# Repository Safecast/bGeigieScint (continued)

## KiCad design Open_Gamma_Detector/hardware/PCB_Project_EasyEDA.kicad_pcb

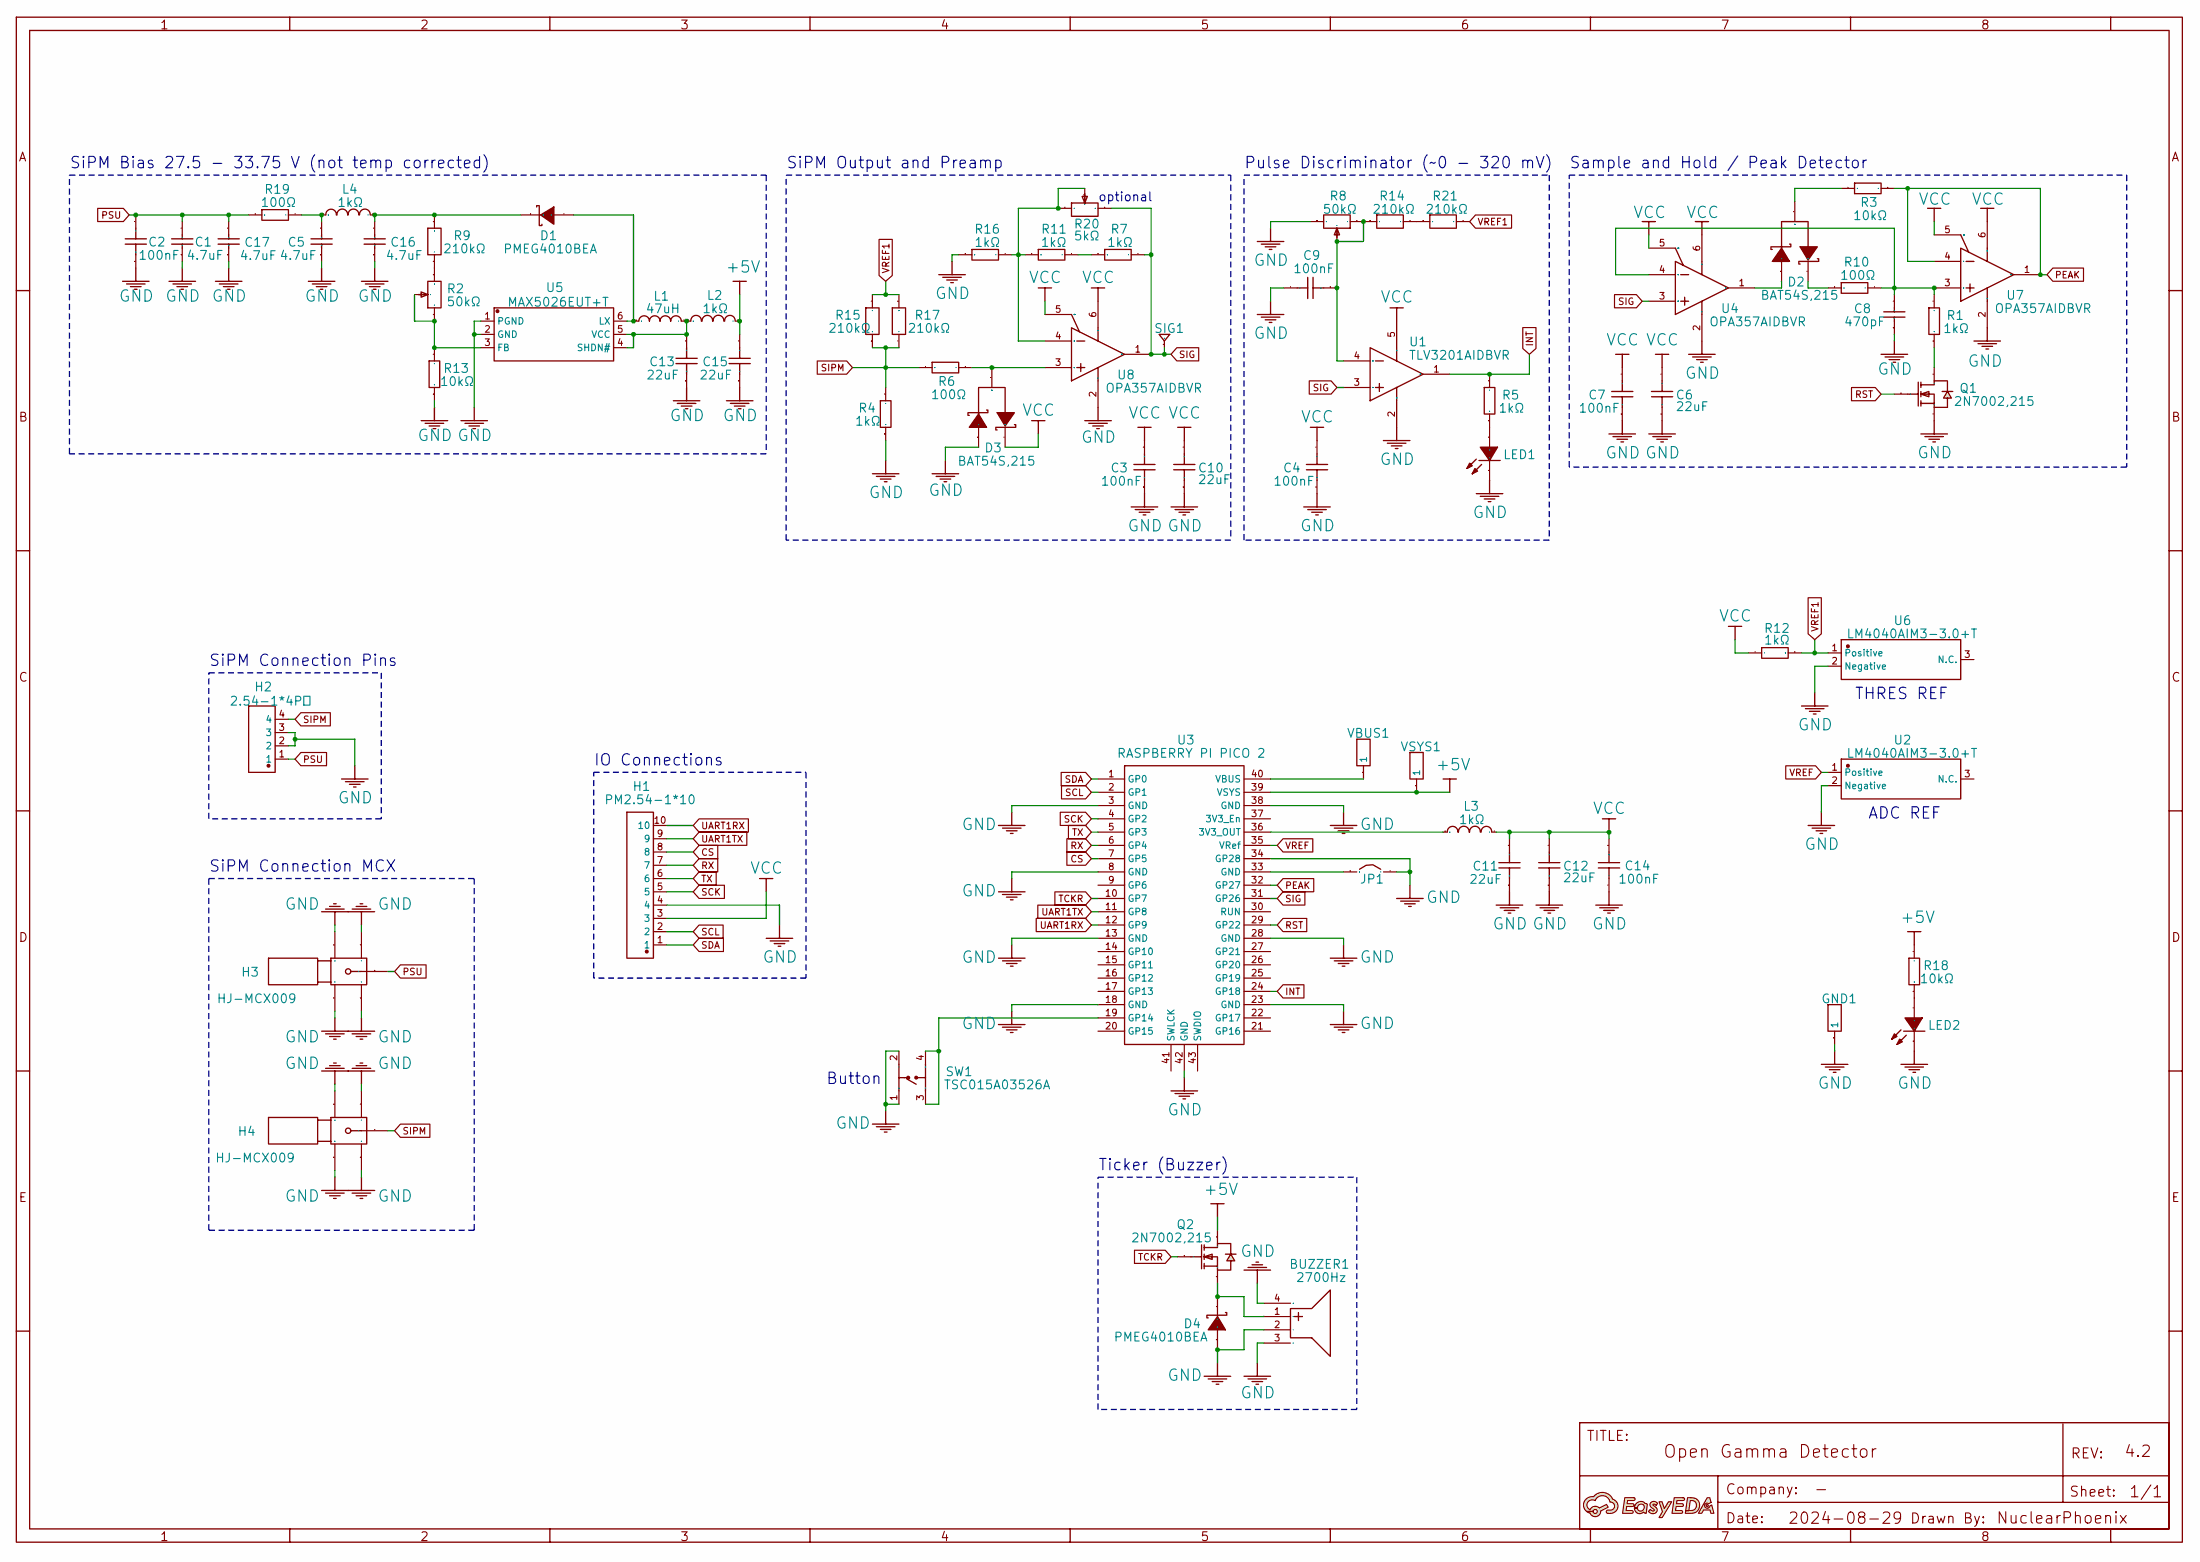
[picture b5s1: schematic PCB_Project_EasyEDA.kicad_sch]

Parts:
BUZZER1: 2700Hz; Manufacturer Part MLT-7525
C1, C5, C16, C17: 4.7uF; Manufacturer Part CL21A475KBQNNNE
C2, C3, C4, C7, C9, C14: 100nF; Manufacturer Part CL10B104KC8NNNC
C6, C10, C11, C12, C13, C15: 22uF; Manufacturer Part CL10A226MP8NUNE
C8: 470pF; Manufacturer Part ECHU1C471JX5
D1, D4: PMEG4010BEA; Manufacturer Part PMEG4010BEA,115
D2, D3: BAT54S,215; Manufacturer Part BAT54S,215
GND1: HDR-M-2.54_1x1
H1: PM2.54-1*10; Manufacturer Part PM2.54-1*10
H2: 2.54-1*4P母; Manufacturer Part 2.54-1*4P母
H3, H4: HJ-MCX009; Manufacturer Part HJ-MCX009
JP1: Jumper
L1: 47uH; Manufacturer Part NRS4018T470MDGJ
L2, L3, L4: 1kΩ; Manufacturer Part BLM18KG102SN1D
LED1, LED2: LTST-C190KGKT; Manufacturer Part LTST-C190KGKT
NO1: NO; Manufacturer Part ?
Q1, Q2: 2N7002,215; Manufacturer Part 2N7002,215
R1, R4, R5, R7, R11, R12, R16: 1kΩ; Manufacturer Part ARG03BTC1001
R2, R8: 50kΩ; Manufacturer Part 3296W-1-503LF
R3, R13, R18: 10kΩ; Manufacturer Part ARG03FTC1002
R6, R10, R19: 100Ω; Manufacturer Part 0603WAF1000T5E
R9, R14, R15, R17, R21: 210kΩ; Manufacturer Part TC0325D2103T5H
R20: 5kΩ; Manufacturer Part 3314J-1-502E
SIG1: TEST-POINT
SW1: TSC015A03526A; Manufacturer Part TSC015A03526A
U1: TLV3201AIDBVR; Manufacturer Part TLV3201AIDBVR
U2, U6: LM4040AIM3-3.0+T; Manufacturer Part LM4040AIM3-3.0+T
U3: RASPBERRY PI PICO 2; Manufacturer Part SC1631
U4, U7, U8: OPA357AIDBVR; Manufacturer Part OPA357AIDBVR
U5: MAX5026EUT+T; Manufacturer Part MAX5026EUT+T
VBUS1: HDR-M-2.54_1x1
VSYS1: HDR-M-2.54_1x1

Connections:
+5V: C15.2, L2.2, Q2.3 (D), R18.2, U3.39 (VSYS), VSYS1.1
CS: H1.8, U3.7 (GP5)
GND: BUZZER1.2 (-), BUZZER1.3, BUZZER1.4, C1.1, C2.1, C3.1, C4.1, C5.1, C6.1, C7.1, C8.1, C9.2, C10.1, C11.1, C12.1, C13.1, C14.2, C15.1, C16.1, C17.1, D3.1 (A), D4.2 (A), GND1.1, H1.4, H2.2, H2.3, H3.1, H3.2, H3.3, H3.4, H4.1, H4.2, H4.3, H4.4, JP1.2, LED1.1 (-), LED2.1 (-), Q1.2 (S), R4.1, R8.1, R13.1, R16.1, SW1.1, SW1.2, U1.2 (GND), U2.2 (Negative), U3.3 (GND), U3.8 (GND), U3.13 (GND), U3.18 (GND), U3.23 (GND), U3.28 (GND), U3.34 (GP28), U3.38 (GND), U3.42 (GND), U4.2 (V-), U5.1 (PGND), U5.2 (GND), U6.2 (Negative), U7.2 (V-), U8.2 (V-); also elsewhere on the board
INT: R5.2, U1.1 (OUT), U3.24 (GP18)
unnamed: BUZZER1.1 (+), D4.1 (K), Q2.2 (S)
unnamed: C5.2, L4.1, R19.2
unnamed: D1.2 (A), L1.1, U5.6 (LX)
unnamed: C16.2, D1.1 (K), L4.2, R9.1
unnamed: D2.1 (A), U4.1 (OUT)
unnamed: D2.3 (AK), R3.2
unnamed: D2.2 (K), R10.1
unnamed: D3.3 (AK), R6.2, U8.3 (IN+)
unnamed: JP1.1, U3.33 (GND)
unnamed: LED1.2 (+), R5.1
unnamed: LED2.2 (+), R18.1
unnamed: Q1.3 (D), R1.1
unnamed: R2.1, R9.2
unnamed: R7.1, R11.2
unnamed: R14.2, R21.1
unnamed: C9.1, R8.2, R8.3, R14.1, U1.4 (IN-)
unnamed: L3.1, U3.36 (3V3_OUT)
unnamed: SW1.3, SW1.4, U3.19 (GP14)
unnamed: U3.40 (VBUS), VBUS1.1
unnamed: C8.2, R1.2, R10.2, U4.4 (IN-), U7.3 (IN+)
unnamed: R2.2, R2.3, R13.2, U5.3 (FB)
unnamed: C13.2, L1.2, L2.1, U5.4 (SHDN#), U5.5 (VCC)
unnamed: R11.1, R16.2, R20.2, R20.3, U8.4 (IN-)
PEAK: R3.1, U3.32 (GP27), U7.1 (OUT), U7.4 (IN-)
PSU: C1.2, C2.2, C17.2, H2.1, H3.5, R19.1
RST: Q1.1 (G), U3.29 (GP22)
RX: H1.7, U3.6 (GP4)
SCK: H1.5, U3.4 (GP2)
SCL: H1.2, U3.2 (GP1)
SDA: H1.1, U3.1 (GP0)
SIG: R7.2, R20.1, SIG1.1, U1.3 (IN+), U3.31 (GP26), U4.3 (IN+), U8.1 (OUT)
SIPM: H2.4, H4.5, R4.2, R6.1, R15.1, R17.2
TCKR: Q2.1 (G), U3.10 (GP7)
TX: H1.6, U3.5 (GP3)
UART1RX: H1.10, U3.12 (GP9)
UART1TX: H1.9, U3.11 (GP8)
VCC: C3.2, C4.2, C6.2, C7.2, C10.2, C11.2, C12.2, C14.1, D3.2 (K), H1.3, L3.2, R12.2, U1.5 (VCC), U4.5 (ENABLE), U4.6 (V+), U7.5 (ENABLE), U7.6 (V+), U8.5 (ENABLE), U8.6 (V+)
VREF: U2.1 (Positive), U3.35 (VRef)
VREF1: R12.1, R15.2, R17.1, R21.2, U6.1 (Positive)

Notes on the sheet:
ADC REF
SiPM Connection Pins
IO Connections
Pulse Discriminator (~0 - 320 mV)
Button
Ticker (Buzzer)
SiPM Output and Preamp
optional
SiPM Bias 27.5 - 33.75 V (not temp corrected)
THRES REF
Sample and Hold / Peak Detector
SiPM Connection MCX

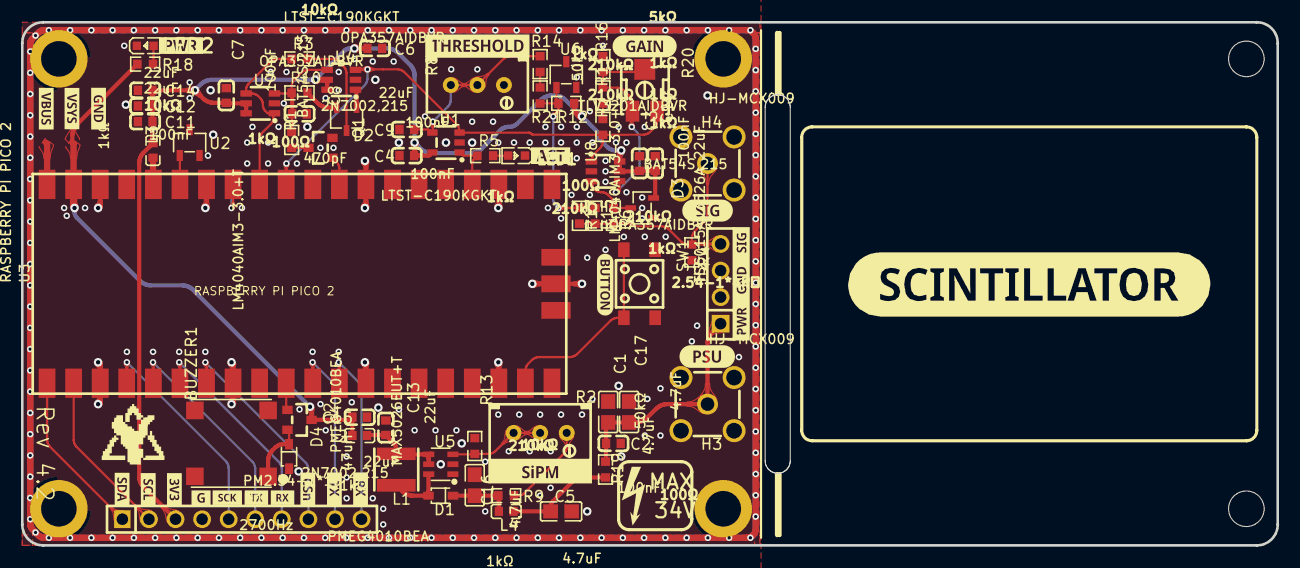
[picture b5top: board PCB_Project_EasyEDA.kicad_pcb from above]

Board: 4 copper layers, 120.0 x 50.0 mm, 71 parts (1 on the bottom side), 42 nets.

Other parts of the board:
Hole_gge75923: Hole_gge75923
Hole_gge92807: Hole_gge92807
Pad_gge138383: Pad_gge138383
Pad_gge138410: Pad_gge138410
Pad_gge138431: Pad_gge138431
Pad_gge138452: Pad_gge138452

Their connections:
GND: Pad_gge138383.1, Pad_gge138410.1, Pad_gge138431.1, Pad_gge138452.1; also elsewhere on the board

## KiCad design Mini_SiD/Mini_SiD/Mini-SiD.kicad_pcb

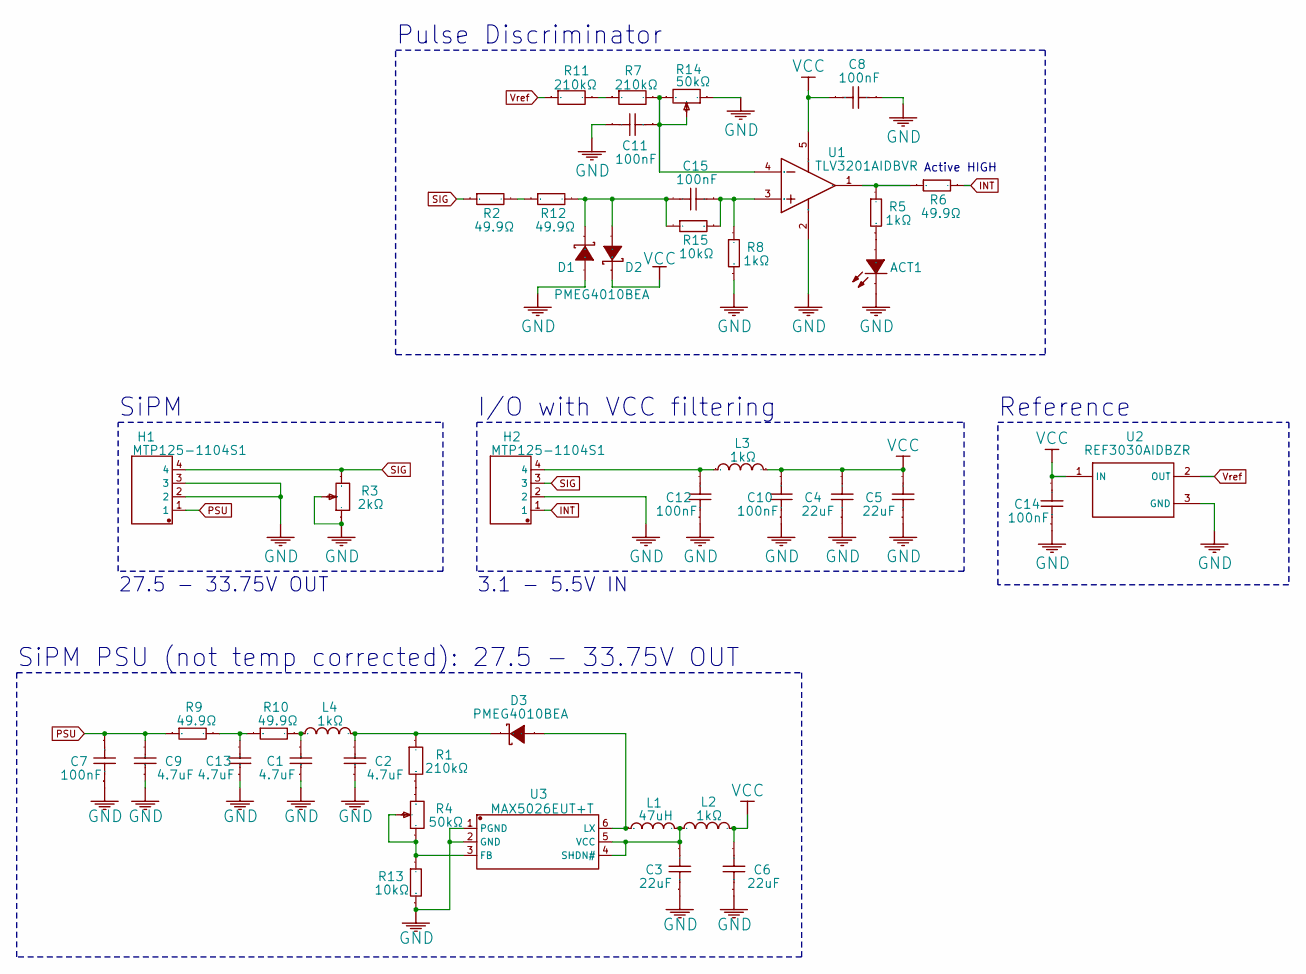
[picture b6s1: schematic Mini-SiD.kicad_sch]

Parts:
ACT1: LTST-C190KGKT; Manufacturer Part LTST-C190KGKT
C1, C2, C9, C13: 4.7uF; Manufacturer Part CL21A475KBQNNNE
C3, C4, C5, C6: 22uF; Manufacturer Part CL10A226MP8NUNE
C7, C8, C10, C11, C12, C14, C15: 100nF; Manufacturer Part CL10B104KC8NNNC
D1, D2, D3: PMEG4010BEA; Manufacturer Part PMEG4010BEA,115
H1, H2: MTP125-1104S1; Manufacturer Part MTP125-1104S1
L1: 47uH; Manufacturer Part NRS4018T470MDGJ
L2, L3, L4: 1kΩ; Manufacturer Part BLM18KG102SN1D
R1, R7, R11: 210kΩ; Manufacturer Part TC0325D2103T5H
R2, R6, R9, R10, R12: 49.9Ω; Manufacturer Part 0603WAF499JT5E
R3: 2kΩ; Manufacturer Part 3362P-1-202LF
R4, R14: 50kΩ; Manufacturer Part 3362P-1-503LF
R5, R8: 1kΩ; Manufacturer Part 0603WAJ0102T5E
R13, R15: 10kΩ; Manufacturer Part ARG03FTC1002
U1: TLV3201AIDBVR; Manufacturer Part TLV3201AIDBVR
U2: REF3030AIDBZR; Manufacturer Part REF3030AIDBZR
U3: MAX5026EUT+T; Manufacturer Part MAX5026EUT+T

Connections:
GND: ACT1.1 (-), C1.1, C2.1, C3.1, C4.1, C5.1, C6.1, C7.1, C8.2, C9.1, C10.1, C11.2, C12.1, C13.1, C14.1, D1.2 (A), H1.2, H1.3, H2.2, R3.2, R3.3, R8.1, R13.1, R14.3, U1.2 (GND), U2.3 (GND), U3.1 (PGND), U3.2 (GND); also elsewhere on the board
INT: H2.1, R6.2
unnamed: ACT1.2 (+), R5.1
unnamed: C1.2, L4.1, R10.2
unnamed: C12.2, H2.4, L3.1
unnamed: C13.2, R9.2, R10.1
unnamed: C15.2, D1.1 (K), D2.2 (A), R12.2, R15.2
unnamed: D3.2 (A), L1.1, U3.6 (LX)
unnamed: C2.2, D3.1 (K), L4.2, R1.2
unnamed: R1.1, R4.1
unnamed: R7.1, R11.2
unnamed: R2.2, R12.1
unnamed: C15.1, R8.2, R15.1, U1.3 (IN+)
unnamed: C11.1, R7.2, R14.1, R14.2, U1.4 (IN-)
unnamed: R5.2, R6.1, U1.1 (OUT)
unnamed: R4.2, R4.3, R13.2, U3.3 (FB)
unnamed: C3.2, L1.2, L2.1, U3.4 (SHDN#), U3.5 (VCC)
PSU: C7.2, C9.2, H1.1, R9.1
SIG: H1.4, H2.3, R2.1, R3.1
VCC: C4.2, C5.2, C6.2, C8.1, C10.2, C14.2, D2.1 (K), L2.2, L3.2, U1.5 (VCC), U2.1 (IN)
Vref: R11.1, U2.2 (OUT)

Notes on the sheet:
Active HIGH
Reference
I/O with VCC filtering
Pulse Discriminator
27.5 - 33.75V OUT
3.1 - 5.5V IN
SiPM
SiPM PSU (not temp corrected): 27.5 - 33.75V OUT

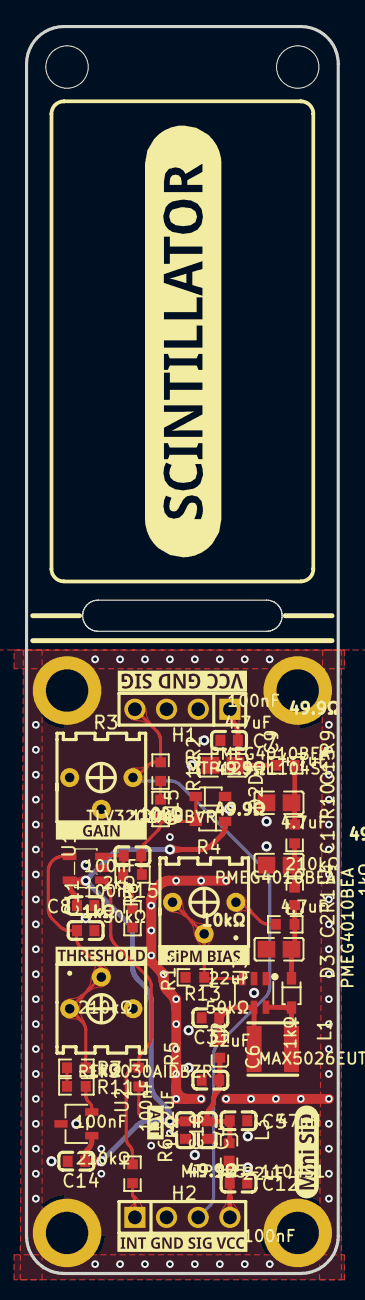
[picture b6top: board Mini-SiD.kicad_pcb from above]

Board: 4 copper layers, 25.0 x 100.0 mm, 48 parts (0 on the bottom side), 20 nets.

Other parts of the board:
Hole_gge8601: Hole_gge8601
Hole_gge14374: Hole_gge14374
Pad_gge4845: Pad_gge4845
Pad_gge5061: Pad_gge5061
Pad_gge8824: Pad_gge8824
Pad_gge8848: Pad_gge8848

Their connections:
GND: Pad_gge4845.1, Pad_gge5061.1, Pad_gge8824.1, Pad_gge8848.1; also elsewhere on the board

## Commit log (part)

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2025-11-18 Added BOM
2025-11-23 Add scripts for board configuration and component placement on PomeloCore PCB
    - Implement `add_board_config.py` to add board outline and upgrade to 4-layer configuration.
    - Create `fix_board_config.py` to correctly place board outline at the end of the file and ensure proper layer configuration.
    - Develop `place_components.py` to automate component placement based on a reference layout, including defined zones and rotations.
    - Introduce `reposition_components.py` to update existing footprint positions on the PCB according to a new layout, ensuring no overlaps.
2025-11-23 Add scripts for backside and frontside silkscreen text, and refine component placement
    - Implemented `add_backside_text.py` to add silkscreen text to the backside of the PomeloCore PCB based on a reference image.
    - Implemented `add_frontside_text.py` to add silkscreen text to the front side of the PomeloCore PCB, including branding and component labels.
    - Created `refine_placement.py` to update component positions based on a detailed top-side reference image, improving layout organization and alignment.
2025-11-23 Added older version
2025-11-23 Moved some components
2025-11-25 docs: update firmware architecture documentation
2025-11-29 Refactor code structure for improved readability and maintainability
2025-11-29 Update credits in README.md to acknowledge original designer and repository
2025-11-29 Update README.md for improved clarity and organization
2025-11-29 Reorganize project structure by moving files into bGeigieScint directory and updating paths in README.md
2025-12-04 docs: Add guide for building a CsI(Tl) scintillator and VS Code workspace configuration.
2025-12-04 CsI(Tl) 10×10×30mm alternative SiPMs
2025-12-04 docs: Add Bill of Materials markdown and two PDF datasheets for silicon photomultipliers and Advansid.
2025-12-04 docs: Remove introductory text and horizontal rule from CsI(Tl) scintillator build guide.
2025-12-04 docs: Add Pomelo Physics PDF document.
2025-12-04 feat: Add Pomelo Physics KiCad schematic and its corresponding PDF export.
2025-12-04 feat: Update KiCad schema to v9, rename project, and revise component symbols for library migration.
2025-12-04 Started board
2025-12-06 Add AFBRS4N44P014M component to KiCad libraries
    - Created new module file for AFBRS4N44P014M in Kicad libs with detailed footprint and pad definitions.
    - Added corresponding module entry in the bGeigieScint.pretty library.
    - Updated fp-lib-table to include new library paths for proper integration.
2025-12-07 Add initial project file for bGeigieScint design
    - Created bGeigieScint.kicad_prl file to define project settings and configurations.
    - Configured board properties including active layer, visibility settings, and opacity.
    - Set up net inspector panel preferences for better net management.
    - Included schematic selection filters for improved design navigation.
2025-12-07 Progress on switching the ESP32 C3 supper mini
2025-12-07 updated check ok
2025-12-07 Updated dates
2025-12-07 Cleaned up
2025-12-08 refactor: Remove unused schematic symbol definitions, add a 3D model, and update KiCad schematic and PCB files.
2025-12-09 config: set PlatformIO upload speed and update VS Code workspace folder path.
2025-12-12 Add bootloader update for Pomelo C37721D with new firmware
2025-12-17 Move Sammy pinout diagram, add Sammy schematic, and update workspace folder path.
2025-12-17 test: Replace main application with a blink test, back up original main.c, and update platformio configuration.
2025-12-18 Add recovery guide and OpenOCD configuration files for ATSAML21G18B
    - Created RECOVERY_GUIDE.md detailing step-by-step recovery methods for unbricking the ATSAML21G18B device.
    - Added openocd_recovery_erase.cfg for basic chip erase functionality.
    - Introduced openocd_recovery_reset.cfg for connecting under reset to enhance recovery success.
    - Implemented openocd_recovery_slow.cfg for low-speed connection to improve reliability during recovery.
2025-12-18 Add UART test script for PomeloCore
    This commit introduces a new Python script, test_uart.py, designed to test UART communication with the PomeloCore. The script opens a specified serial port, sends a series of commands, and displays t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
2025-12-26 Add README for ESP32-C3 migration with setup instructions and architecture changes
2025-12-27 feat: introduce ESP32-C3 Super Mini GPIO mapping documentation and minimal HAL header.
2025-12-27 chore: Add bGeigieScint backup file.
2025-12-28 feat: Switch from PWM to Sigma-Delta Modulation for analog output and document ESP32-S2 internal DACs.
2025-12-31 feat: Add new KiCad component libraries and update schematic/PCB.
2025-12-31 feat: Assign footprints to schematic components, add a new net, and place pin headers on the PCB while adjusting a mounting hole.
2025-12-31 Remove an unused GND label and update component units with added datasheet links for multiple components in schematics.
2026-01-14 Added 3d model files, how to build files, etc
2026-01-26 feat: Update ESP32-C3 SuperMini Kicad symbol and footprint with clarified pin assignments and properties, and include Kicad libs in the workspace.
2026-01-29 Added OpenGamma and Mii-SiD project in Kicad files.
2026-01-29 New folders
2026-01-29 Update submodule pointers: Mini_SiD and Open_Gamma_Detector
2026-01-29 feat: Add auto-approve setting for terminal in workspace configuration
2026-02-06 This version of Antigravity is no longer supported. Please update to receive the latest features!
2026-02-06 - Added initial entries for various components including capacitors, resistors, and headers.T right angle counts
2026-03-27 Update CMSIS documentation, DSP library examples, and SAML21 microcontroller support files.
2026-03-27 Remove file `deleted`.
2026-03-27 chore: delete an unspecified file.
